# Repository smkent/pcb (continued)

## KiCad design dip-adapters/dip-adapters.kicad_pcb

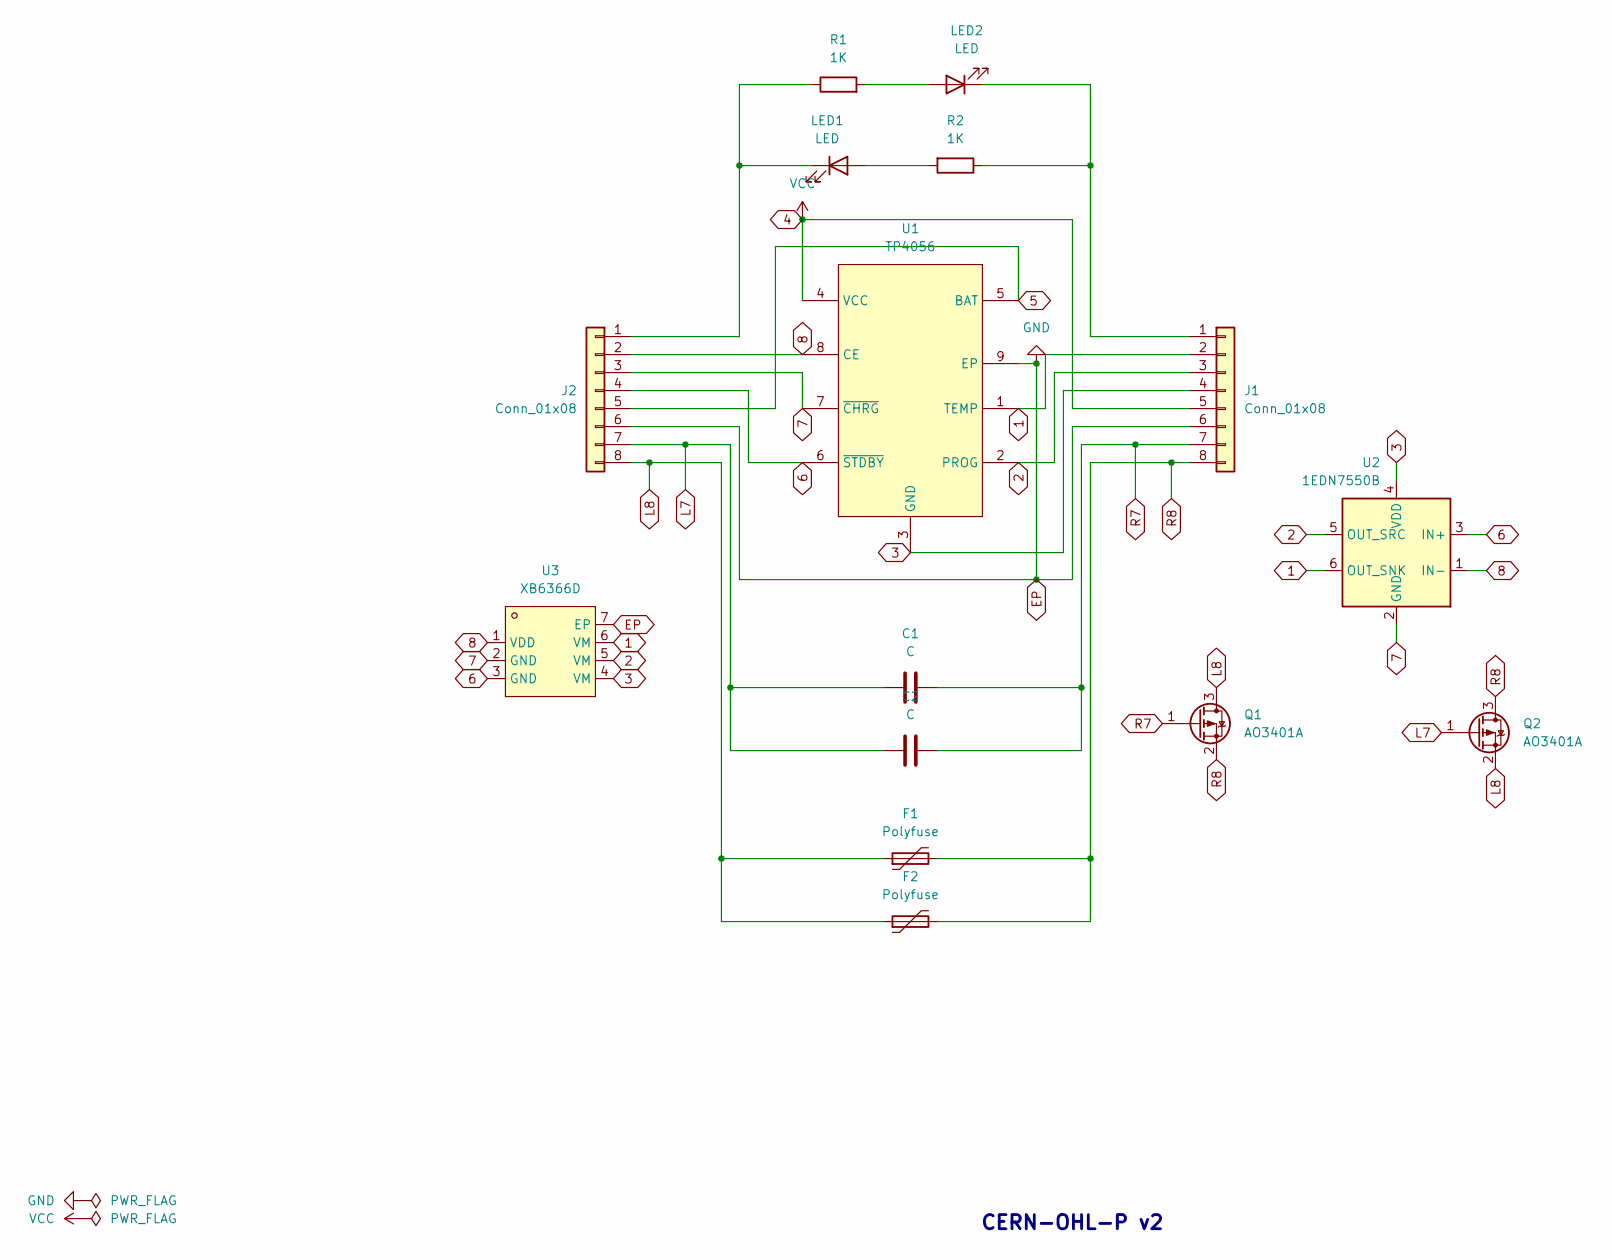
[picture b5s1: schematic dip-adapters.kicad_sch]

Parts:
C1, C2: C; C_0805_2012Metric_Pad1.18x1.45mm_HandSolder
F1, F2: Polyfuse; Fuse_1206_3216Metric_Pad1.42x1.75mm_HandSolder
J1, J2: Conn_01x08; PinHeader_1x08_P2.54mm_Vertical_simple
LED1, LED2: LED; LED_0805_2012Metric_Pad1.15x1.40mm_HandSolder_simple
Q1, Q2: AO3401A; SOT-23
R1, R2: 1K; R_0805_2012Metric_Pad1.20x1.40mm_HandSolder
U1: TP4056; SOIC-8-1EP_3.9x4.9mm_P1.27mm_EP2.41x3.3mm_ThermalVias_Custo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; LCSC Part C16581
U2: 1EDN7550B; SOT-23-6
U3: XB6366D; DFN-6_L2.0-W2.0-P0.65-BL-EP_ThermalVias_HandSolder; LCSC Part C2760016

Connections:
1: J1.2, U1.1 (TEMP), U2.6 (OUT_SNK), U3.6 (VM)
2: J1.3, U1.2 (PROG), U2.5 (OUT_SRC), U3.5 (VM)
3: J1.4, U1.3 (GND), U2.4 (VDD), U3.4 (VM)
4: J1.5, U1.4 (VCC)
5: J2.5, U1.5 (BAT)
6: J2.4, U1.6 (~STDBY), U2.3 (IN+), U3.3 (GND)
7: J2.3, U1.7 (~CHRG), U2.2 (GND), U3.2 (GND)
8: J2.2, U1.8 (CE), U2.1 (IN-), U3.1 (VDD)
EP: J1.6, J2.6, U1.9 (EP), U3.7 (EP)
L7: C1.1, C2.1, J2.7, Q2.1 (G)
L8: F1.1, F2.1, J2.8, Q1.3 (D), Q2.2 (S)
unnamed: J1.1, LED2.1 (K), R2.1
unnamed: J2.1, LED1.1 (K), R1.1
unnamed: LED1.2 (A), R2.2
unnamed: LED2.2 (A), R1.2
R7: C1.2, C2.2, J1.7, Q1.1 (G)
R8: F1.2, F2.2, J1.8, Q1.2 (S), Q2.3 (D)

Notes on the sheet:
CERN-OHL-P v2

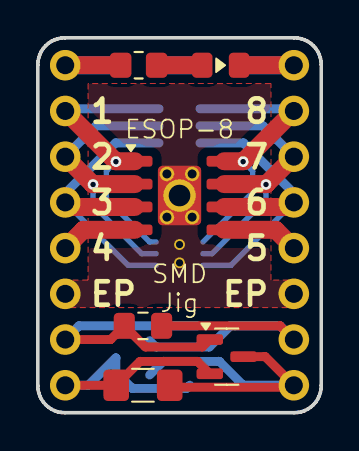
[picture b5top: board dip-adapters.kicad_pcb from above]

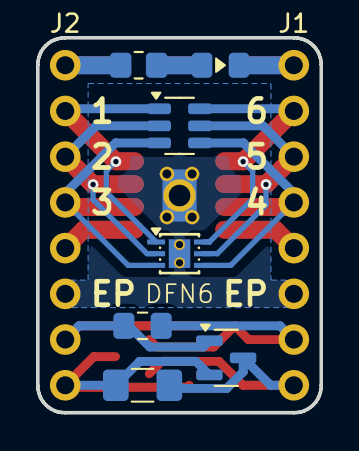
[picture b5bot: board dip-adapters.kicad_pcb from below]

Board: 2 copper layers, 15.7 x 20.8 mm, 15 parts (9 on the bottom side), 17 nets.

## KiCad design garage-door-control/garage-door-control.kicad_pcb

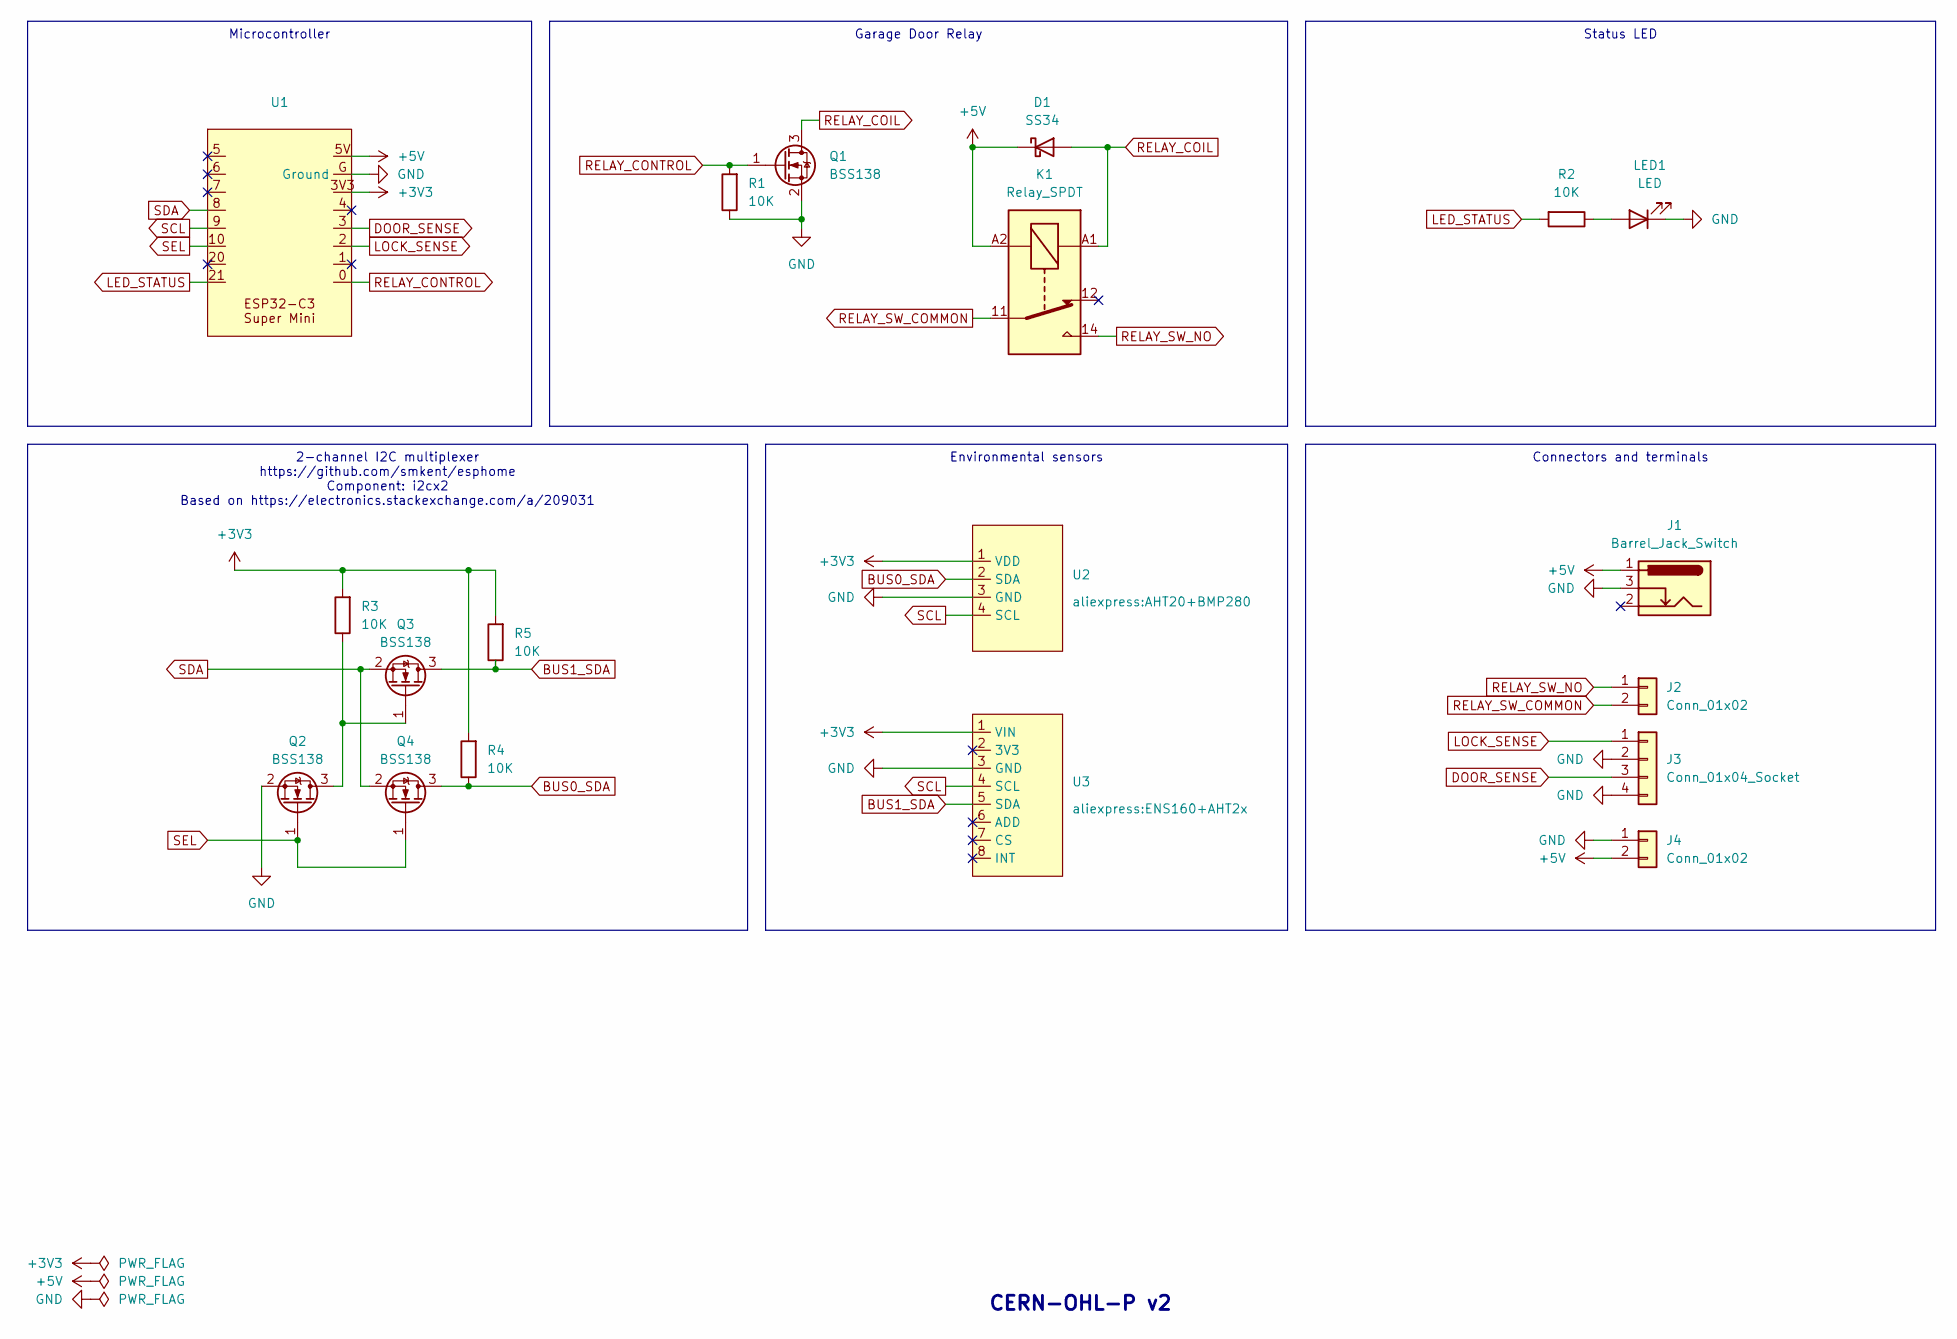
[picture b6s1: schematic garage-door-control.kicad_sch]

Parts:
D1: SS34; D_SMA_simple
J1: Barrel_Jack_Switch; BarrelJack_CLIFF_FC681465S_SMT_Horizontal
J2: Conn_01x02; JST_XH_B2B-XH-A_1x02_P2.50mm_Vertical
J3: Conn_01x04_Socket; JST_XH_B4B-XH-A_1x04_P2.50mm_Vertical
J4: Conn_01x02; TerminalBlock_Phoenix_MKDS-1,5-2-5.08_1x02_P5.08mm_Horizont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
K1: Relay_SPDT; Relay_SPDT_Hongfa_HF3F-L-xx-1ZL1T
LED1: LED; LED_0805_2012Metric_Pad1.15x1.40mm_HandSolder_simple
Q1, Q2, Q3, Q4: BSS138; SOT-23
R1, R2, R3, R4, R5: 10K; R_0805_2012Metric_Pad1.20x1.40mm_HandSolder
U1: ESP32-C3-Super-Mini-Pins
U2: AHT20+BMP280
U3: ENS160+AHT2x

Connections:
+3V3: R3.2, R4.2, R5.2, U1.3V3, U2.1 (VDD), U3.1 (VIN)
+5V: D1.1 (K), J1.1, J4.2, K1.A2, U1.5V
BUS0_SDA: Q4.3 (D), R4.1, U2.2 (SDA)
BUS1_SDA: Q3.3 (D), R5.1, U3.5 (SDA)
DOOR_SENSE: J3.3, U1.3
GND: J1.3, J3.2, J3.4, J4.1, LED1.1 (K), Q1.2 (S), Q2.2 (S), R1.1, U1.G (Ground), U2.3 (GND), U3.3 (GND)
LED_STATUS: R2.2, U1.21
LOCK_SENSE: J3.1, U1.2
unnamed: LED1.2 (A), R2.1
unnamed: Q2.3 (D), Q3.1 (G), R3.1
RELAY_COIL: D1.2 (A), K1.A1, Q1.3 (D)
RELAY_CONTROL: Q1.1 (G), R1.2, U1.0
RELAY_SW_COMMON: J2.2, K1.11
RELAY_SW_NO: J2.1, K1.14
SCL: U1.9, U2.4 (SCL), U3.4 (SCL)
SDA: Q3.2 (S), Q4.2 (S), U1.8
SEL: Q2.1 (G), Q4.1 (G), U1.10

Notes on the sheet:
Garage Door Relay
2-channel I2C multiplexer https://github.com/smkent/esphome Component: i2cx2 Based on https://electronics.stackexchange.com/a/209031
Environmental sensors
Microcontroller
Status LED
Connectors and terminals
CERN-OHL-P v2

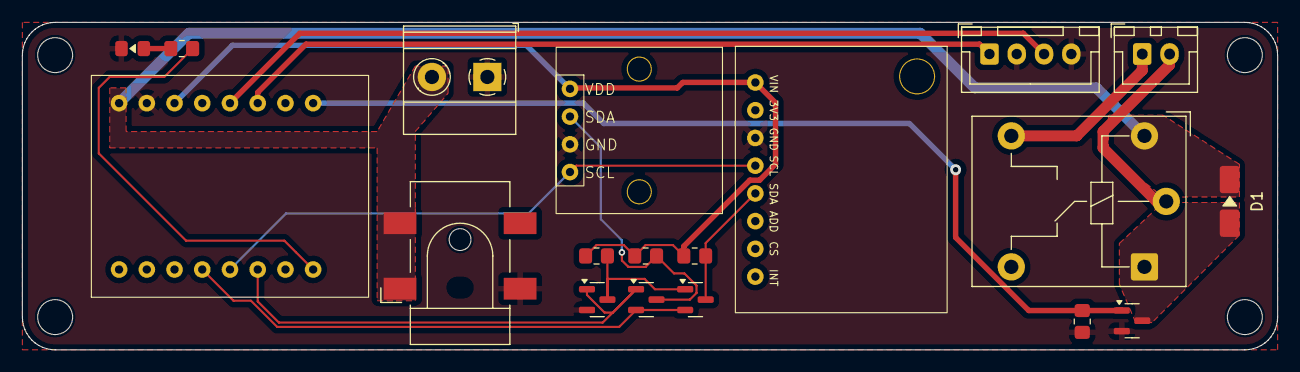
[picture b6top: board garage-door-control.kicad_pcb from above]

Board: 2 copper layers, 115.0 x 30.0 mm, 19 parts (0 on the bottom side), 17 nets.

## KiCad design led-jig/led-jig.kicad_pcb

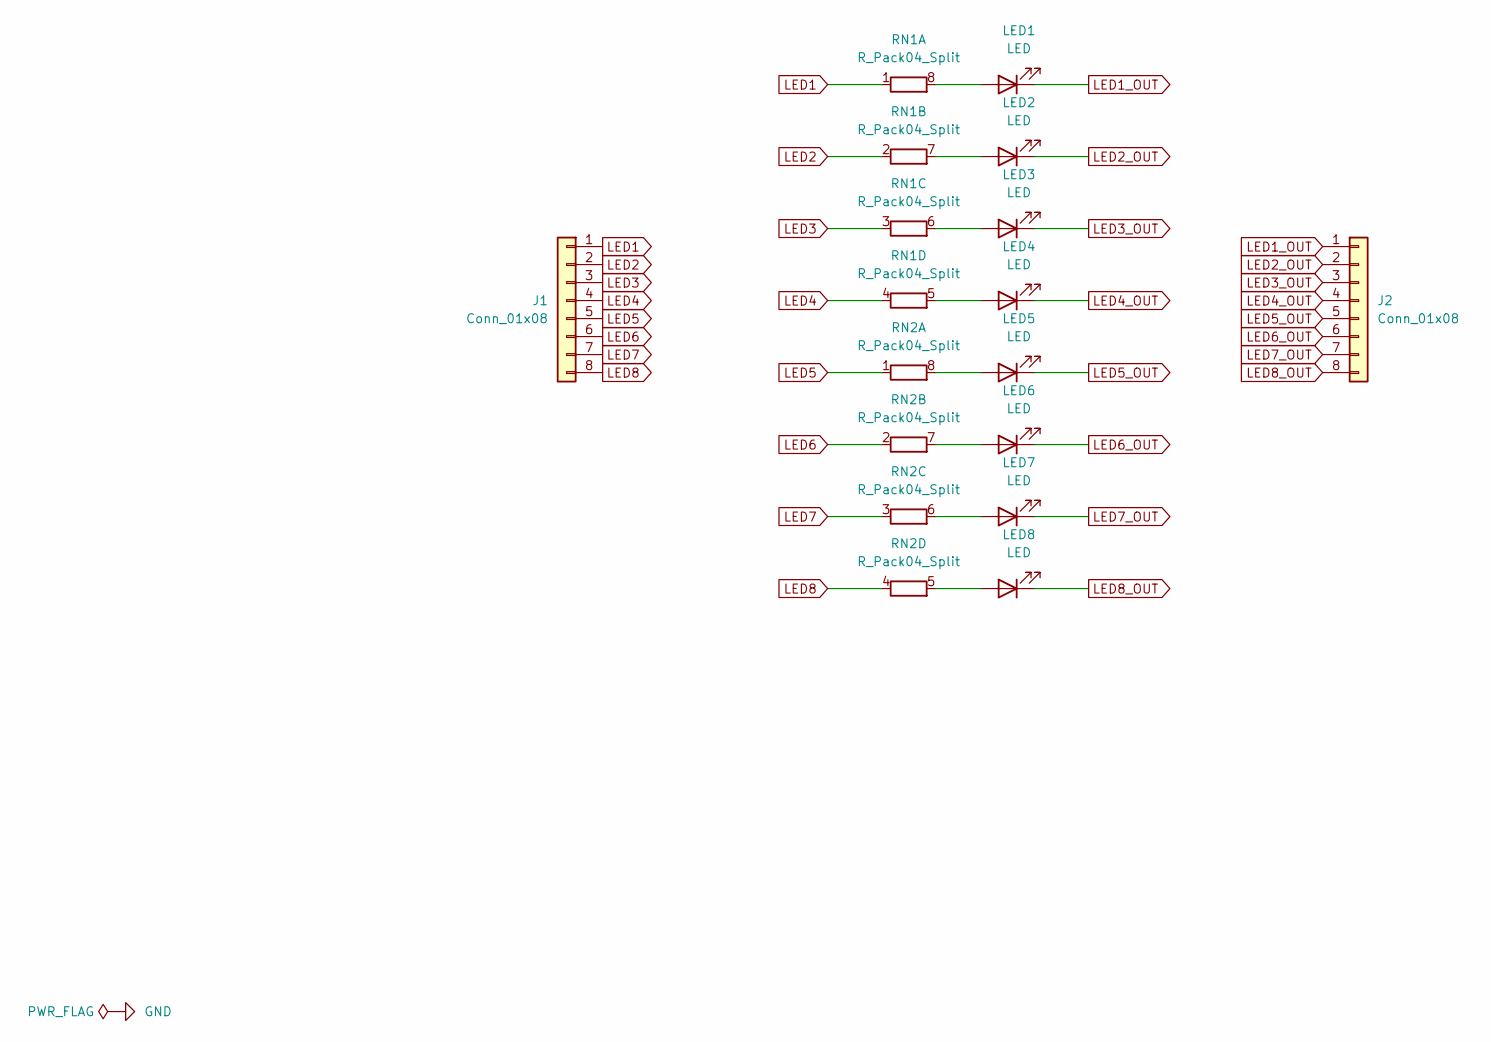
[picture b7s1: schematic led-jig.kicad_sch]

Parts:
J1, J2: Conn_01x08; PinHeader_1x08_P2.54mm_Vertical_simple
LED1, LED2, LED3, LED4, LED5, LED6, LED7, LED8: LED; LED_0805_2012Metric_Pad1.15x1.40mm_HandSolder_simple
RN1, RN2: R_Pack04_Split; R_Array_Convex_4x0603

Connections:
LED1: J1.1, RN1.1 (R1.1)
LED1_OUT: J2.1, LED1.1 (K)
LED2: J1.2, RN1.2 (R2.1)
LED2_OUT: J2.2, LED2.1 (K)
LED3: J1.3, RN1.3 (R3.1)
LED3_OUT: J2.3, LED3.1 (K)
LED4: J1.4, RN1.4 (R4.1)
LED4_OUT: J2.4, LED4.1 (K)
LED5: J1.5, RN2.1 (R1.1)
LED5_OUT: J2.5, LED5.1 (K)
LED6: J1.6, RN2.2 (R2.1)
LED6_OUT: J2.6, LED6.1 (K)
LED7: J1.7, RN2.3 (R3.1)
LED7_OUT: J2.7, LED7.1 (K)
LED8: J1.8, RN2.4 (R4.1)
LED8_OUT: J2.8, LED8.1 (K)
unnamed: LED1.2 (A), RN1.8 (R1.2)
unnamed: LED2.2 (A), RN1.7 (R2.2)
unnamed: LED3.2 (A), RN1.6 (R3.2)
unnamed: LED4.2 (A), RN1.5 (R4.2)
unnamed: LED5.2 (A), RN2.8 (R1.2)
unnamed: LED6.2 (A), RN2.7 (R2.2)
unnamed: LED7.2 (A), RN2.6 (R3.2)
unnamed: LED8.2 (A), RN2.5 (R4.2)

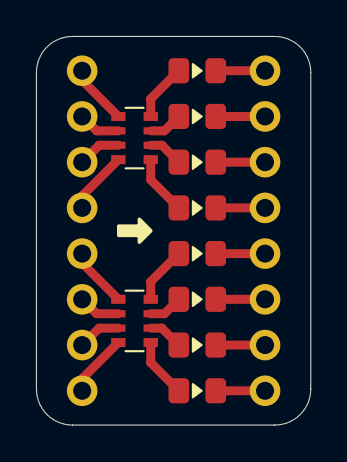
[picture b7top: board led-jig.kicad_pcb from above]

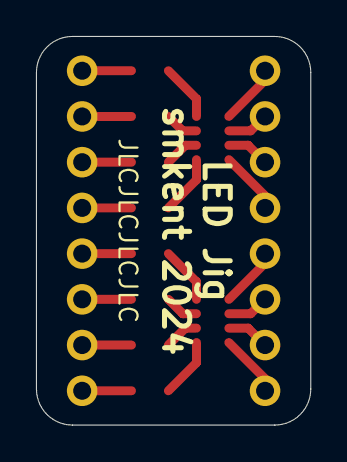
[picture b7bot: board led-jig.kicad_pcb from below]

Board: 2 copper layers, 15.2 x 21.6 mm, 12 parts (2 on the bottom side), 24 nets.

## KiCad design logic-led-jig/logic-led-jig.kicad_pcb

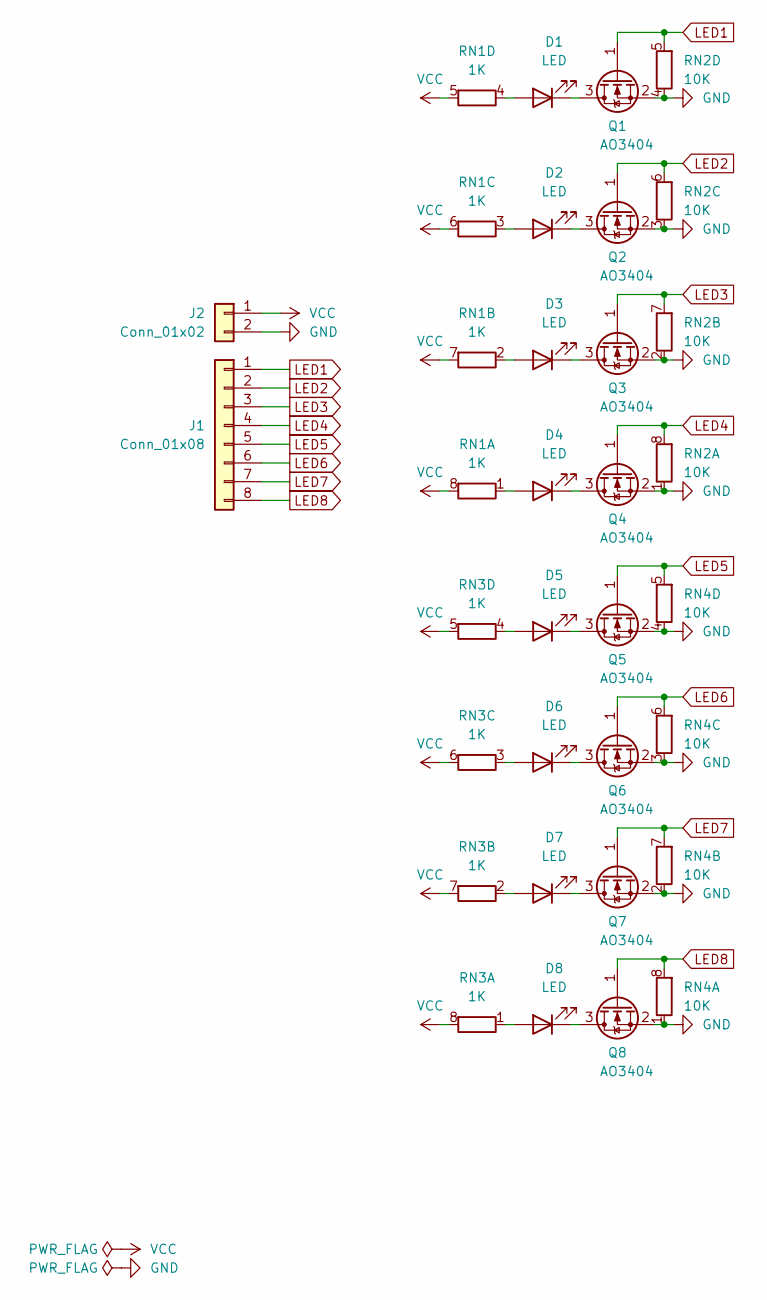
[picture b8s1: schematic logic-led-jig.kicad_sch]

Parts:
D1, D2, D3, D4, D5, D6, D7, D8: LED; LED_0805_2012Metric_simple
J1: Conn_01x08; PinHeader_1x08_P2.54mm_Vertical_simple
J2: Conn_01x02; PinHeader_1x02_P2.54mm_Vertical_simple_pad2gnd
Q1, Q2, Q3, Q4, Q5, Q6, Q7, Q8: AO3404; SOT-23
RN1, RN3: 1K; R_Array_Convex_4x0603
RN2, RN4: 10K; R_Array_Convex_4x0603

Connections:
GND: J2.2, Q1.2 (S), Q2.2 (S), Q3.2 (S), Q4.2 (S), Q5.2 (S), Q6.2 (S), Q7.2 (S), Q8.2 (S), RN2.1 (R1.1), RN2.2 (R2.1), RN2.3 (R3.1), RN2.4 (R4.1), RN4.1 (R1.1), RN4.2 (R2.1), RN4.3 (R3.1), RN4.4 (R4.1)
LED1: J1.1, Q1.1 (G), RN2.5 (R4.2)
LED2: J1.2, Q2.1 (G), RN2.6 (R3.2)
LED3: J1.3, Q3.1 (G), RN2.7 (R2.2)
LED4: J1.4, Q4.1 (G), RN2.8 (R1.2)
LED5: J1.5, Q5.1 (G), RN4.5 (R4.2)
LED6: J1.6, Q6.1 (G), RN4.6 (R3.2)
LED7: J1.7, Q7.1 (G), RN4.7 (R2.2)
LED8: J1.8, Q8.1 (G), RN4.8 (R1.2)
unnamed: D1.2 (A), RN1.4 (R4.1)
unnamed: D1.1 (K), Q1.3 (D)
unnamed: D2.2 (A), RN1.3 (R3.1)
unnamed: D2.1 (K), Q2.3 (D)
unnamed: D3.2 (A), RN1.2 (R2.1)
unnamed: D3.1 (K), Q3.3 (D)
unnamed: D4.2 (A), RN1.1 (R1.1)
unnamed: D4.1 (K), Q4.3 (D)
unnamed: D5.2 (A), RN3.4 (R4.1)
unnamed: D5.1 (K), Q5.3 (D)
unnamed: D6.2 (A), RN3.3 (R3.1)
unnamed: D6.1 (K), Q6.3 (D)
unnamed: D7.2 (A), RN3.2 (R2.1)
unnamed: D7.1 (K), Q7.3 (D)
unnamed: D8.2 (A), RN3.1 (R1.1)
unnamed: D8.1 (K), Q8.3 (D)
VCC: J2.1, RN1.5 (R4.2), RN1.6 (R3.2), RN1.7 (R2.2), RN1.8 (R1.2), RN3.5 (R4.2), RN3.6 (R3.2), RN3.7 (R2.2), RN3.8 (R1.2)

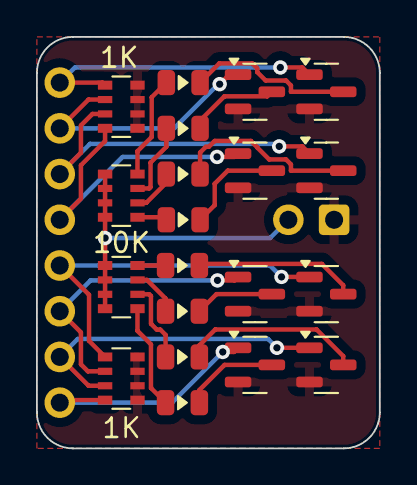
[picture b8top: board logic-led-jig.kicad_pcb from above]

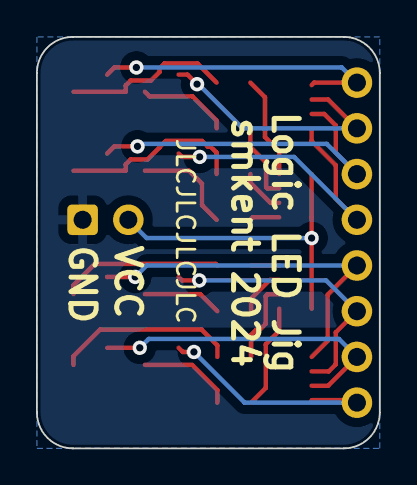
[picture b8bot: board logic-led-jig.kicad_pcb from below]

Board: 2 copper layers, 19.1 x 22.9 mm, 22 parts (2 on the bottom side), 26 nets.
